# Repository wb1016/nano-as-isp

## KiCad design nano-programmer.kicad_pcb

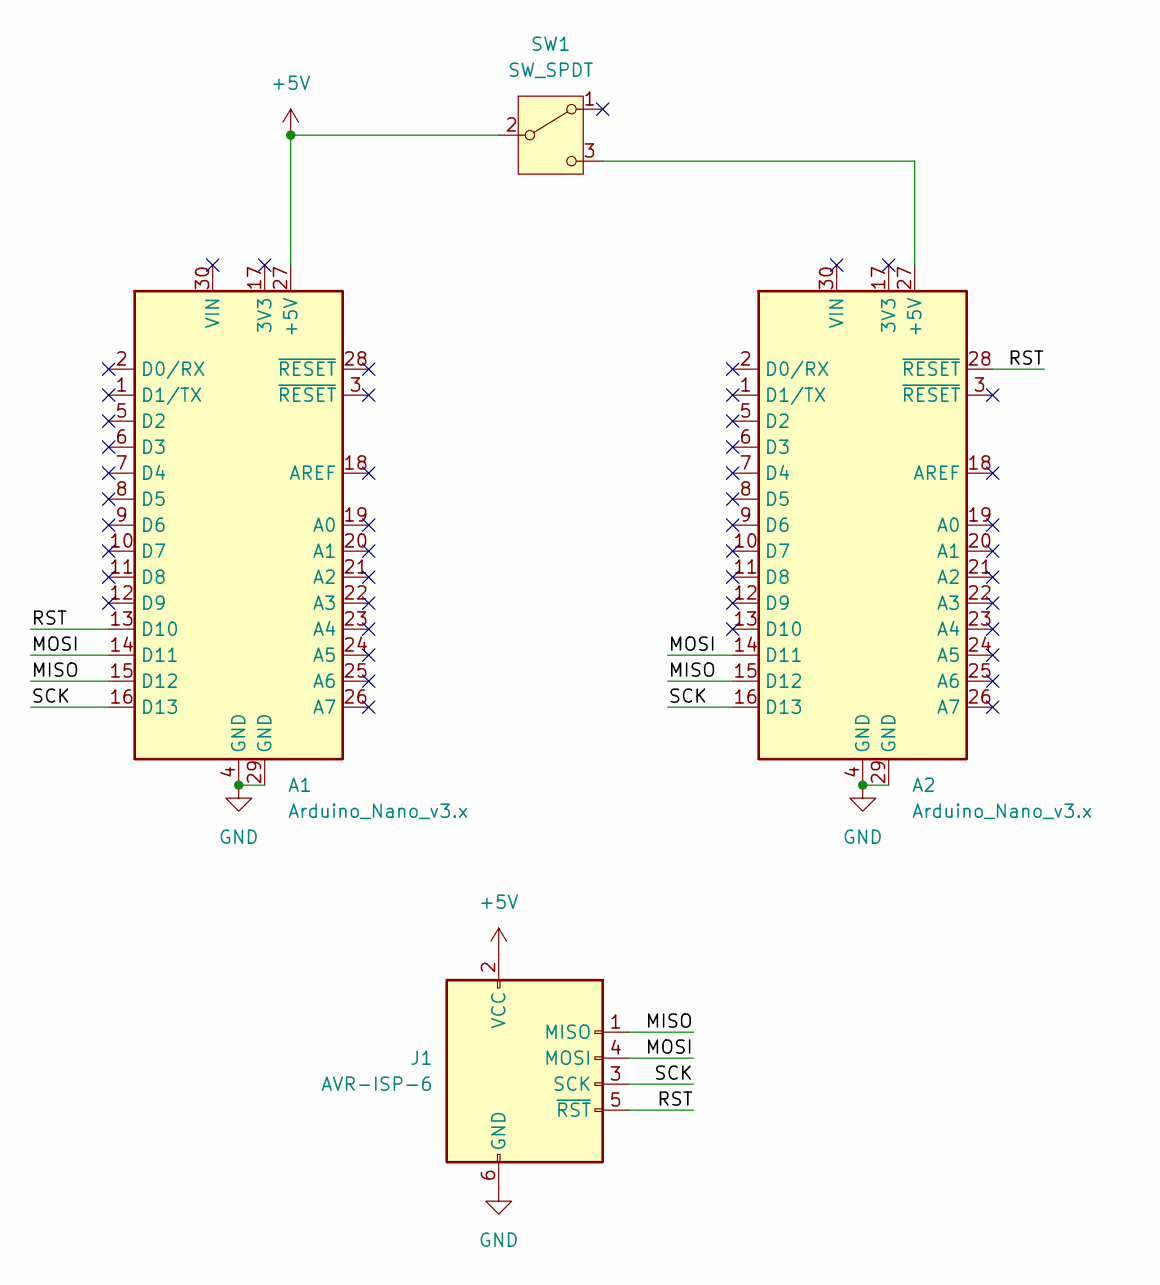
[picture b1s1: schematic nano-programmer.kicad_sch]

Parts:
A1, A2: Arduino_Nano_v3.x; Arduino_Nano
J1: AVR-ISP-6; IDC-Header_2x03_P2.54mm_Vertical
SW1: SW_SPDT; PinHeader_1x03_P2.54mm_Vertical

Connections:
+5V: A1.27 (+5V), J1.2 (VCC), SW1.2 (B)
/MISO: A1.15 (D12), A2.15 (D12), J1.1 (MISO)
/MOSI: A1.14 (D11), A2.14 (D11), J1.4 (MOSI)
/RST: A1.13 (D10), A2.28 (~RESET), J1.5 (~RST)
/SCK: A1.16 (D13), A2.16 (D13), J1.3 (SCK)
GND: A1.4 (GND), A1.29 (GND), A2.4 (GND), A2.29 (GND), J1.6 (GND)
unnamed: A2.27 (+5V), SW1.3 (C)

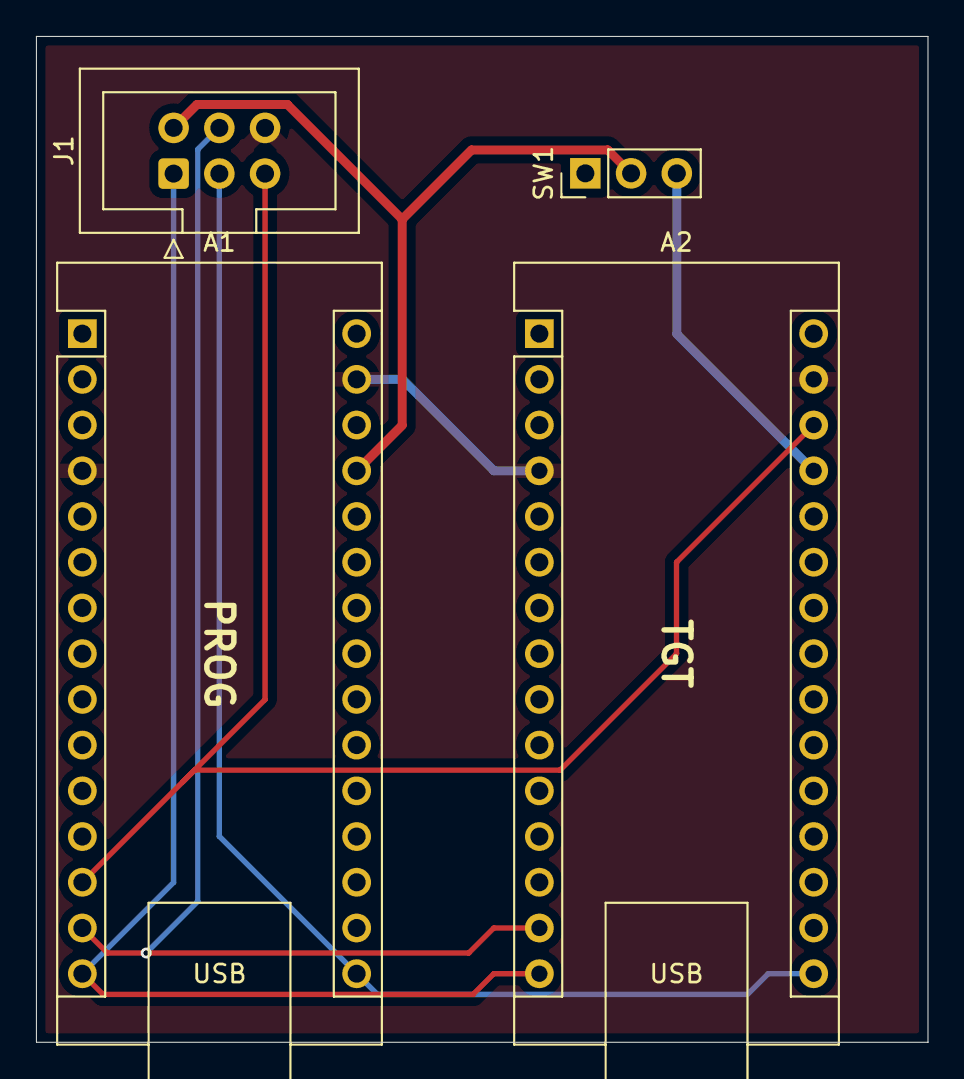
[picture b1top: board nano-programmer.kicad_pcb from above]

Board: 2 copper layers, 49.5 x 55.9 mm, 4 parts (0 on the bottom side), 7 nets.

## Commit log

2024-03-11 asdf
2024-05-10 gitignore
